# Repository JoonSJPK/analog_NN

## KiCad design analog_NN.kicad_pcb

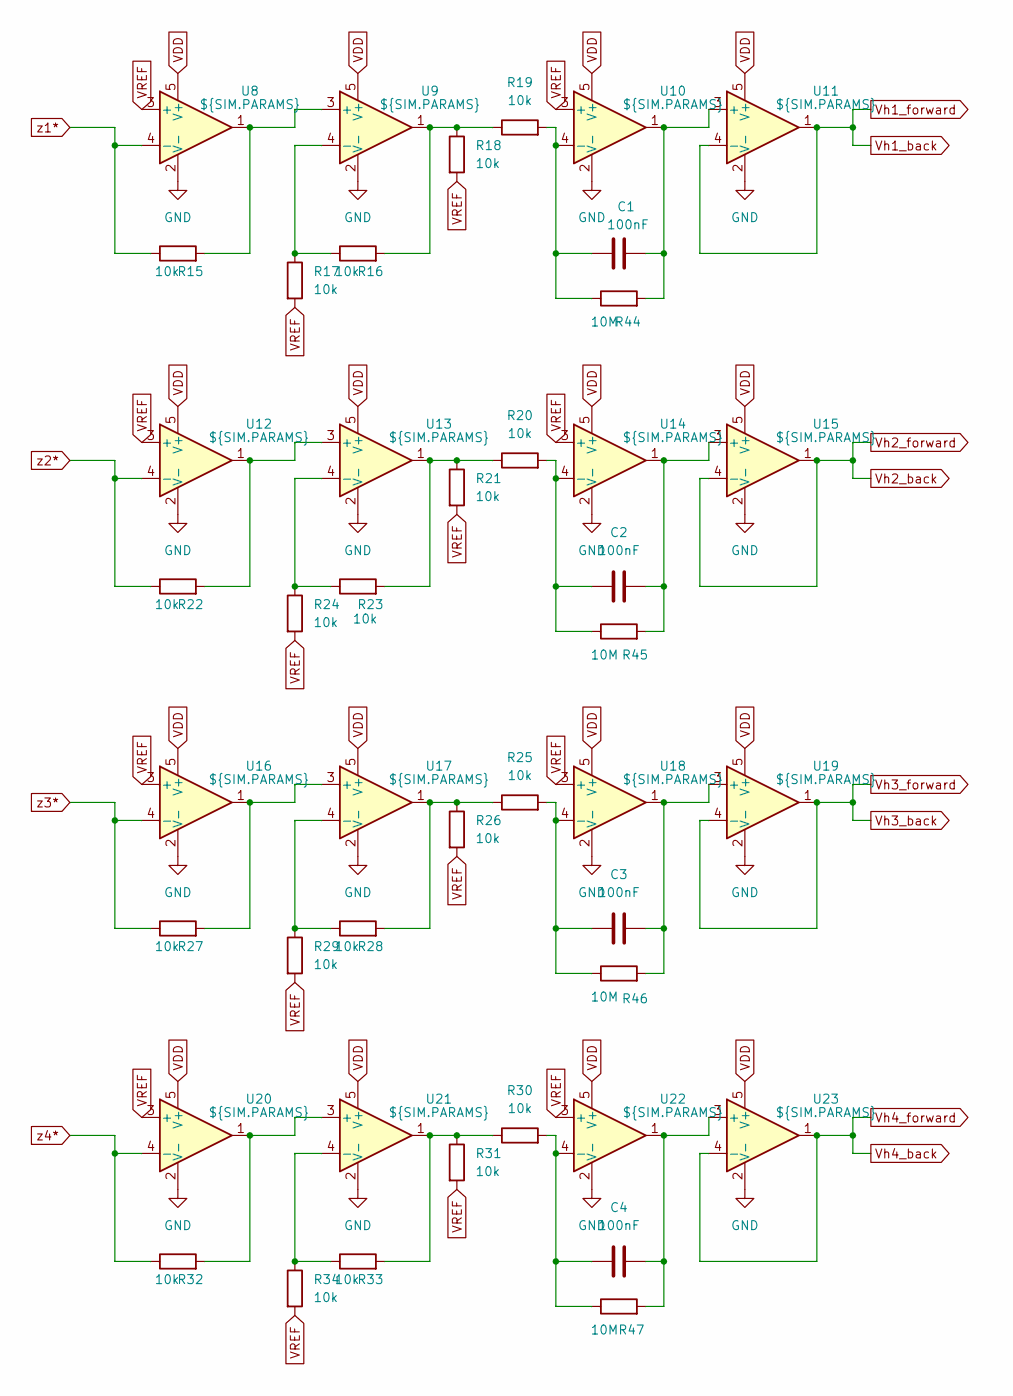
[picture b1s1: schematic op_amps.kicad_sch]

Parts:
C1, C2, C3, C4: 100nF; C_1206_3216Metric
R15, R16, R17, R18, R19, R20, R21, R22, R23, R24, R25, R26, R27, R28, R29, R30, R31, R32, R33, R34: 10k; R_1206_3216Metric
R44, R45, R46, R47: 10M; R_1206_3216Metric
U8, U9, U10, U11, U12, U13, U14, U15, U16, U17, U18, U19, U20, U21, U22, U23: ${SIM.PARAMS}; SOT-23-5

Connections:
GND: U8.2 (V-), U9.2 (V-), U10.2 (V-), U11.2 (V-), U12.2 (V-), U13.2 (V-), U14.2 (V-), U15.2 (V-), U16.2 (V-), U17.2 (V-), U18.2 (V-), U19.2 (V-), U20.2 (V-), U21.2 (V-), U22.2 (V-), U23.2 (V-); also elsewhere on the board
unnamed: R16.2, R18.1, R19.1, U9.1
unnamed: R20.1, R21.1, R23.2, U13.1
unnamed: R25.1, R26.1, R28.2, U17.1
unnamed: R30.1, R31.1, R33.2, U21.1
unnamed: R15.2, U8.1, U9.3 (+)
unnamed: R16.1, R17.1, U9.4 (-)
unnamed: C1.1, R19.2, R44.1, U10.4 (-)
unnamed: C1.2, R44.2, U10.1, U11.3 (+)
unnamed: R22.2, U12.1, U13.3 (+)
unnamed: R23.1, R24.1, U13.4 (-)
unnamed: C2.1, R20.2, R45.1, U14.4 (-)
unnamed: C2.2, R45.2, U14.1, U15.3 (+)
unnamed: R27.2, U16.1, U17.3 (+)
unnamed: R28.1, R29.1, U17.4 (-)
unnamed: C3.1, R25.2, R46.1, U18.4 (-)
unnamed: C3.2, R46.2, U18.1, U19.3 (+)
unnamed: R32.2, U20.1, U21.3 (+)
unnamed: R33.1, R34.1, U21.4 (-)
unnamed: C4.1, R30.2, R47.1, U22.4 (-)
unnamed: C4.2, R47.2, U22.1, U23.3 (+)
VDD: U8.5 (V+), U9.5 (V+), U10.5 (V+), U11.5 (V+), U12.5 (V+), U13.5 (V+), U14.5 (V+), U15.5 (V+), U16.5 (V+), U17.5 (V+), U18.5 (V+), U19.5 (V+), U20.5 (V+), U21.5 (V+), U22.5 (V+), U23.5 (V+); also elsewhere on the board
VREF: R17.2, R18.2, R21.2, R24.2, R26.2, R29.2, R31.2, R34.2, U8.3 (+), U10.3 (+), U12.3 (+), U14.3 (+), U16.3 (+), U18.3 (+), U20.3 (+), U22.3 (+); also elsewhere on the board
Vh1: U11.1, U11.4 (-); also elsewhere on the board
Vh2: U15.1, U15.4 (-); also elsewhere on the board
Vh3: U19.1, U19.4 (-); also elsewhere on the board
Vh4: U23.1, U23.4 (-); also elsewhere on the board
cbar1: R15.1, U8.4 (-); also elsewhere on the board
cbar2: R22.1, U12.4 (-); also elsewhere on the board
cbar3: R27.1, U16.4 (-); also elsewhere on the board
cbar4: R32.1, U20.4 (-); also elsewhere on the board

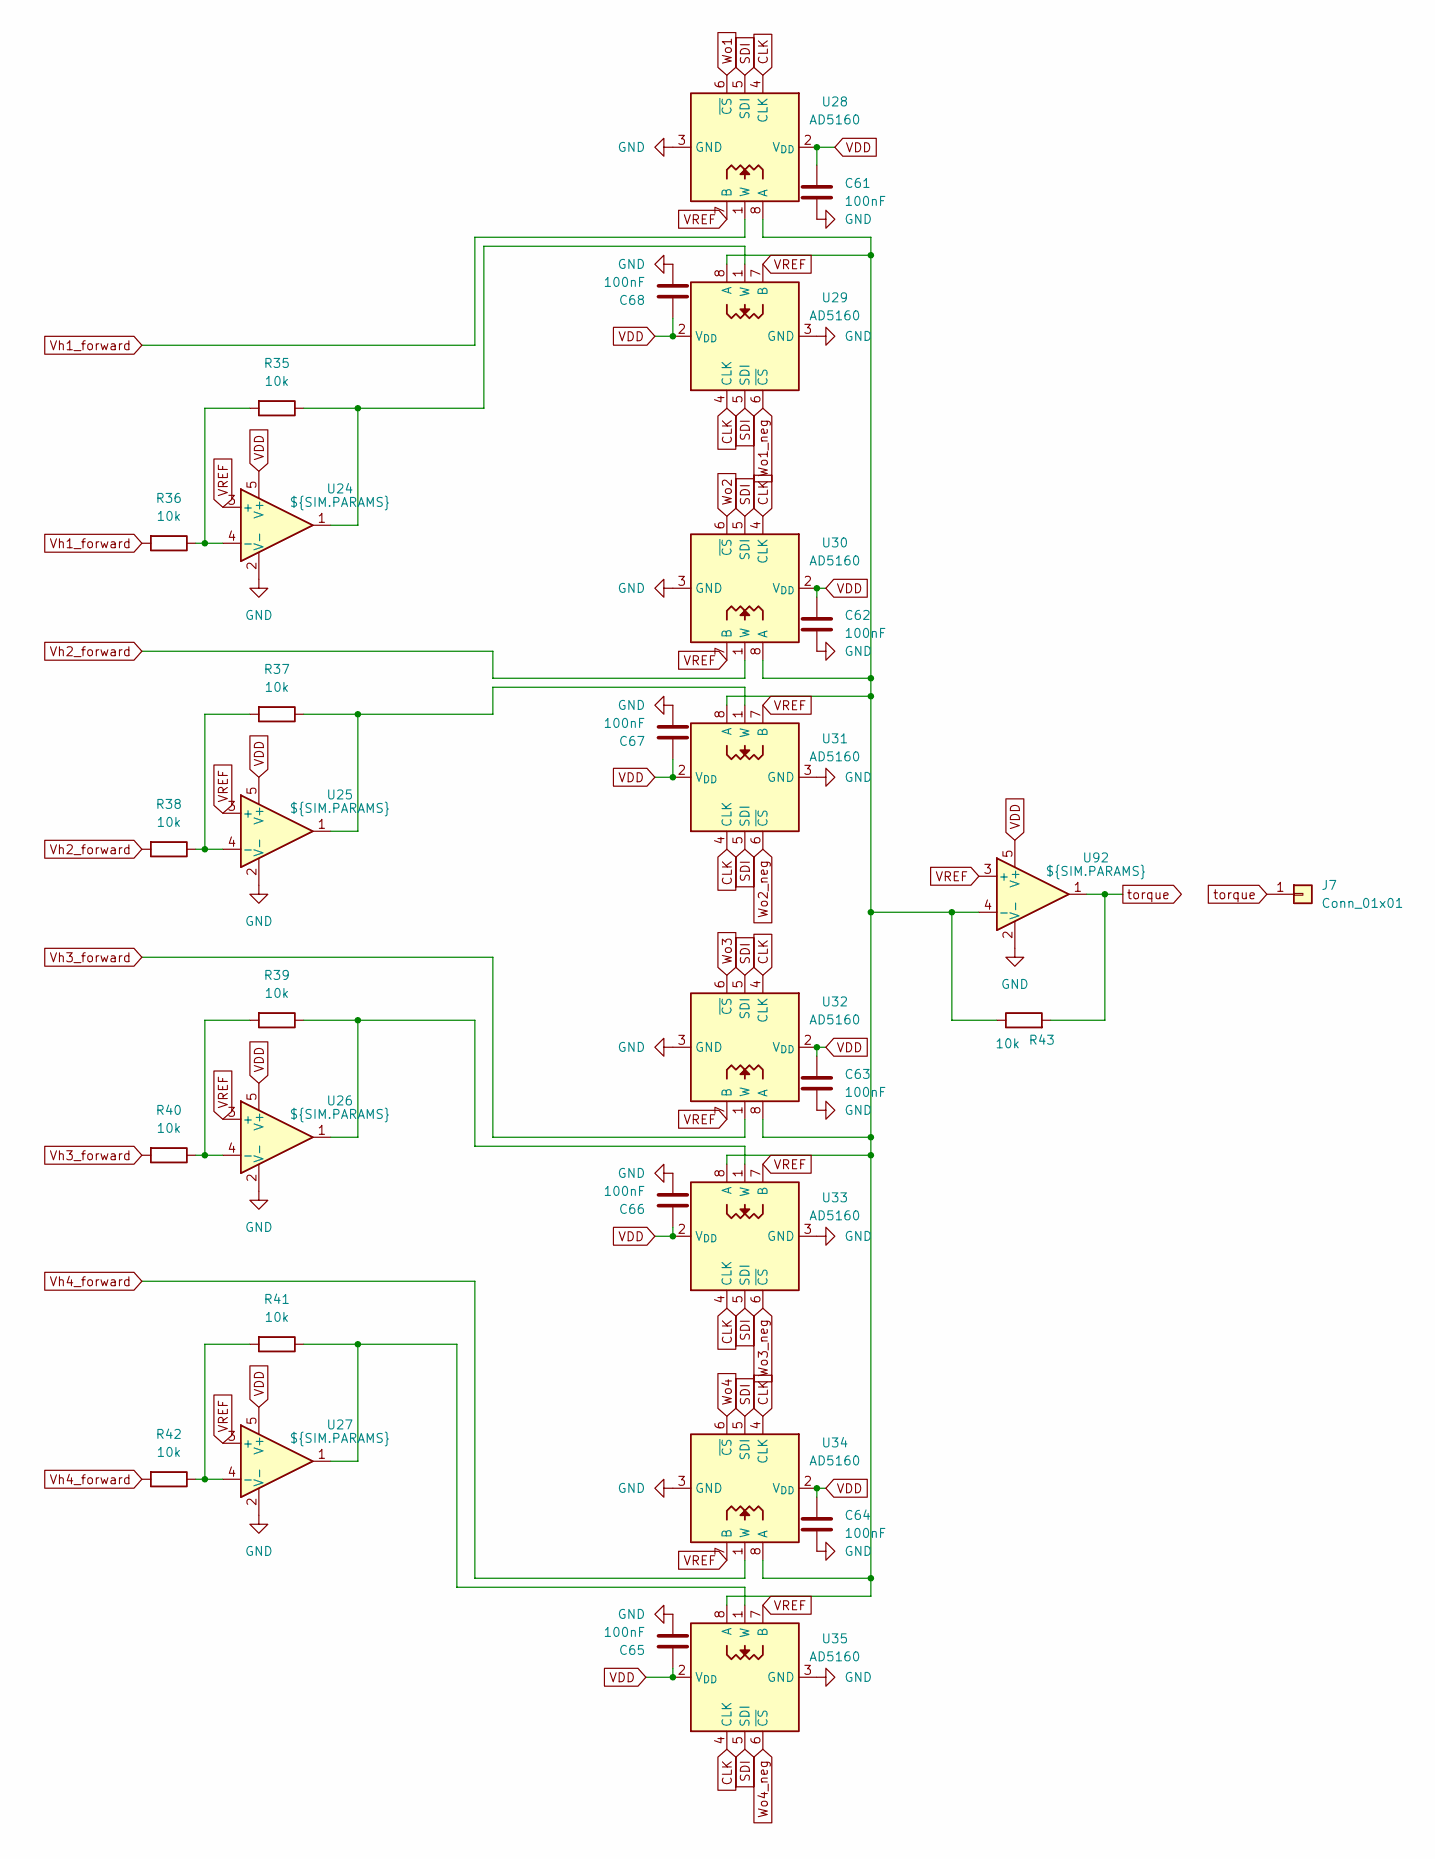
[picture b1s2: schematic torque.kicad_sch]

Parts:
C61, C62, C63, C64, C65, C66, C67, C68: 100nF; C_1206_3216Metric
J7: Conn_01x01; WireSolderPad_1.0mm
R35, R36, R37, R38, R39, R40, R41, R42, R43: 10k; R_1206_3216Metric
U24, U25, U26, U27, U92: ${SIM.PARAMS}; SOT-23-5
U28, U29, U30, U31, U32, U33, U34, U35: AD5160; SOT-23-8

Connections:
CLK: U28.4 (CLK), U29.4 (CLK), U30.4 (CLK), U31.4 (CLK), U32.4 (CLK), U33.4 (CLK), U34.4 (CLK), U35.4 (CLK); also elsewhere on the board
GND: C61.2, C62.2, C63.2, C64.2, C65.2, C66.2, C67.2, C68.2, U24.2 (V-), U25.2 (V-), U26.2 (V-), U27.2 (V-), U28.3 (GND), U29.3 (GND), U30.3 (GND), U31.3 (GND), U32.3 (GND), U33.3 (GND), U34.3 (GND), U35.3 (GND), U92.2 (V-); also elsewhere on the board
unnamed: R35.2, R36.1, U24.4 (-)
unnamed: R37.2, R38.1, U25.4 (-)
unnamed: R39.2, R40.1, U26.4 (-)
unnamed: R41.2, R42.1, U27.4 (-)
unnamed: R43.1, U28.8 (A), U29.8 (A), U30.8 (A), U31.8 (A), U32.8 (A), U33.8 (A), U34.8 (A), U35.8 (A), U92.4 (-)
unnamed: R35.1, U24.1, U29.1 (W)
unnamed: R37.1, U25.1, U31.1 (W)
unnamed: R39.1, U26.1, U33.1 (W)
unnamed: R41.1, U27.1, U35.1 (W)
SDI: U28.5 (SDI), U29.5 (SDI), U30.5 (SDI), U31.5 (SDI), U32.5 (SDI), U33.5 (SDI), U34.5 (SDI), U35.5 (SDI); also elsewhere on the board
VDD: C61.1, C62.1, C63.1, C64.1, C65.1, C66.1, C67.1, C68.1, U24.5 (V+), U25.5 (V+), U26.5 (V+), U27.5 (V+), U28.2 (V_{DD}), U29.2 (V_{DD}), U30.2 (V_{DD}), U31.2 (V_{DD}), U32.2 (V_{DD}), U33.2 (V_{DD}), U34.2 (V_{DD}), U35.2 (V_{DD}), U92.5 (V+); also elsewhere on the board
VREF: U24.3 (+), U25.3 (+), U26.3 (+), U27.3 (+), U28.7 (B), U29.7 (B), U30.7 (B), U31.7 (B), U32.7 (B), U33.7 (B), U34.7 (B), U35.7 (B), U92.3 (+); also elsewhere on the board
Vh1_forward: R36.2, U28.1 (W)
Vh2_forward: R38.2, U30.1 (W)
Vh3_forward: R40.2, U32.1 (W)
Vh4_forward: R42.2, U34.1 (W)
Wo1: U28.6 (~CS); also elsewhere on the board
Wo1_neg: U29.6 (~CS); also elsewhere on the board
Wo2: U30.6 (~CS); also elsewhere on the board
Wo2_neg: U31.6 (~CS); also elsewhere on the board
Wo3: U32.6 (~CS); also elsewhere on the board
Wo3_neg: U33.6 (~CS); also elsewhere on the board
Wo4: U34.6 (~CS); also elsewhere on the board
Wo4_neg: U35.6 (~CS); also elsewhere on the board
torque: J7.1, R43.2, U92.1

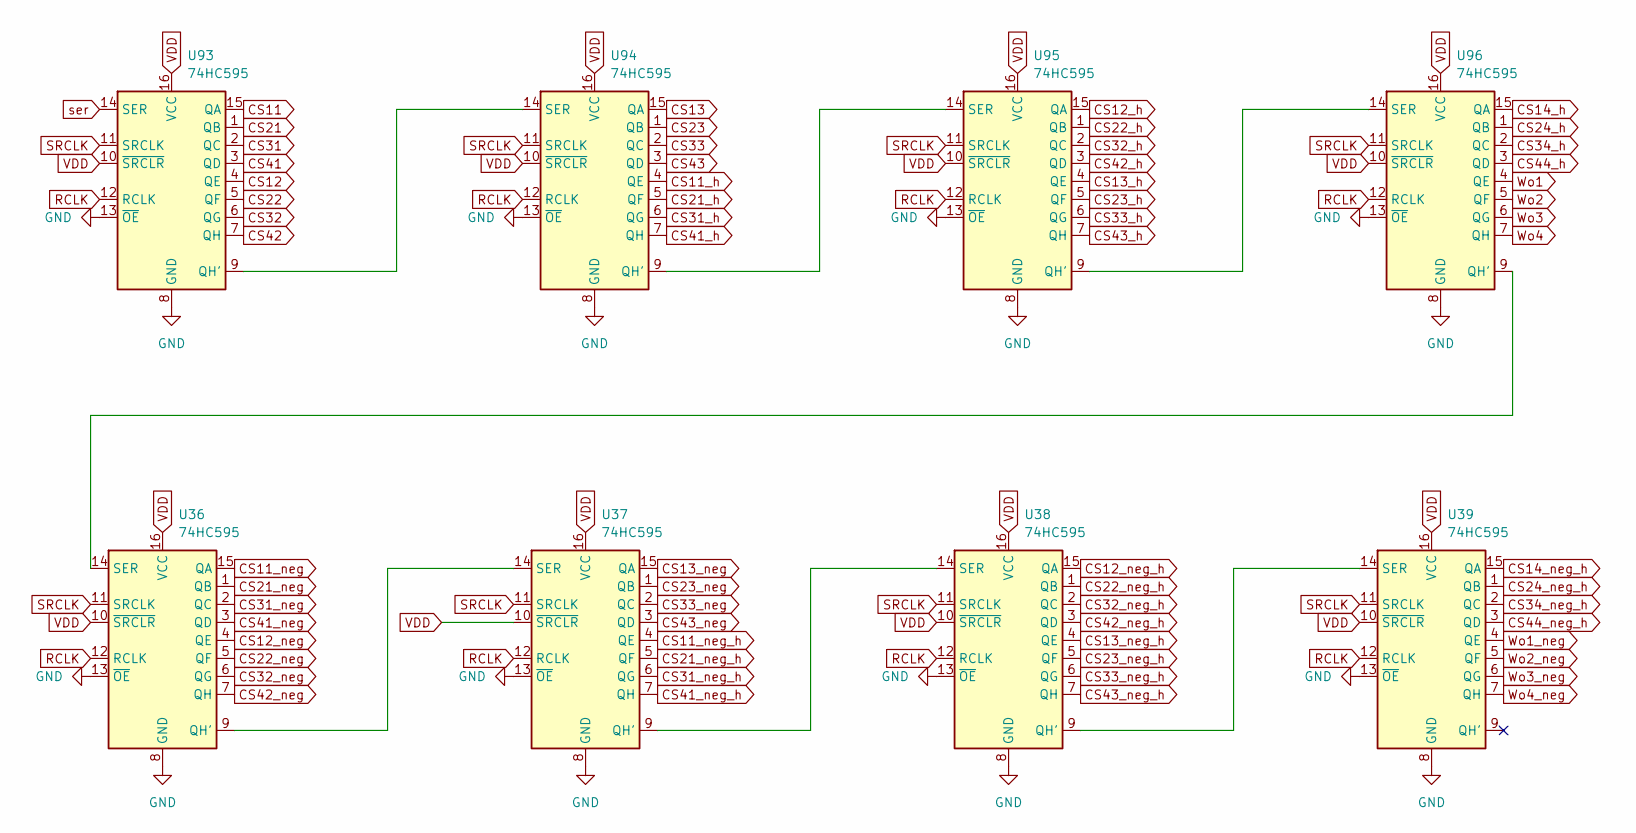
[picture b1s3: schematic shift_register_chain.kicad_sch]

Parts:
U36, U37, U38, U39, U93, U94, U95, U96: 74HC595; SOIC-16_3.9x9.9mm_P1.27mm

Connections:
CS11: U93.15 (QA); also elsewhere on the board
CS11_h: U94.4 (QE); also elsewhere on the board
CS11_neg: U36.15 (QA); also elsewhere on the board
CS11_neg_h: U37.4 (QE); also elsewhere on the board
CS12: U93.4 (QE); also elsewhere on the board
CS12_h: U95.15 (QA); also elsewhere on the board
CS12_neg: U36.4 (QE); also elsewhere on the board
CS12_neg_h: U38.15 (QA); also elsewhere on the board
CS13: U94.15 (QA); also elsewhere on the board
CS13_h: U95.4 (QE); also elsewhere on the board
CS13_neg: U37.15 (QA); also elsewhere on the board
CS13_neg_h: U38.4 (QE); also elsewhere on the board
CS14_h: U96.15 (QA); also elsewhere on the board
CS14_neg_h: U39.15 (QA); also elsewhere on the board
CS21: U93.1 (QB); also elsewhere on the board
CS21_h: U94.5 (QF); also elsewhere on the board
CS21_neg: U36.1 (QB); also elsewhere on the board
CS21_neg_h: U37.5 (QF); also elsewhere on the board
CS22: U93.5 (QF); also elsewhere on the board
CS22_h: U95.1 (QB); also elsewhere on the board
CS22_neg: U36.5 (QF); also elsewhere on the board
CS22_neg_h: U38.1 (QB); also elsewhere on the board
CS23: U94.1 (QB); also elsewhere on the board
CS23_h: U95.5 (QF); also elsewhere on the board
CS23_neg: U37.1 (QB); also elsewhere on the board
CS23_neg_h: U38.5 (QF); also elsewhere on the board
CS24_h: U96.1 (QB); also elsewhere on the board
CS24_neg_h: U39.1 (QB); also elsewhere on the board
CS31: U93.2 (QC); also elsewhere on the board
CS31_h: U94.6 (QG); also elsewhere on the board
CS31_neg: U36.2 (QC); also elsewhere on the board
CS31_neg_h: U37.6 (QG); also elsewhere on the board
CS32: U93.6 (QG); also elsewhere on the board
CS32_h: U95.2 (QC); also elsewhere on the board
CS32_neg: U36.6 (QG); also elsewhere on the board
CS32_neg_h: U38.2 (QC); also elsewhere on the board
CS33: U94.2 (QC); also elsewhere on the board
CS33_h: U95.6 (QG); also elsewhere on the board
CS33_neg: U37.2 (QC); also elsewhere on the board
CS33_neg_h: U38.6 (QG); also elsewhere on the board
CS34_h: U96.2 (QC); also elsewhere on the board
CS34_neg_h: U39.2 (QC); also elsewhere on the board
CS41: U93.3 (QD); also elsewhere on the board
CS41_h: U94.7 (QH); also elsewhere on the board
CS41_neg: U36.3 (QD); also elsewhere on the board
CS41_neg_h: U37.7 (QH); also elsewhere on the board
CS42: U93.7 (QH); also elsewhere on the board
CS42_h: U95.3 (QD); also elsewhere on the board
CS42_neg: U36.7 (QH); also elsewhere on the board
CS42_neg_h: U38.3 (QD); also elsewhere on the board
CS43: U94.3 (QD); also elsewhere on the board
CS43_h: U95.7 (QH); also elsewhere on the board
CS43_neg: U37.3 (QD); also elsewhere on the board
CS43_neg_h: U38.7 (QH); also elsewhere on the board
CS44_h: U96.3 (QD); also elsewhere on the board
CS44_neg_h: U39.3 (QD); also elsewhere on the board
GND: U36.8 (GND), U36.13 (~OE), U37.8 (GND), U37.13 (~OE), U38.8 (GND), U38.13 (~OE), U39.8 (GND), U39.13 (~OE), U93.8 (GND), U93.13 (~OE), U94.8 (GND), U94.13 (~OE), U95.8 (GND), U95.13 (~OE), U96.8 (GND), U96.13 (~OE); also elsewhere on the board
unnamed: U36.9 (QH'), U37.14 (SER)
unnamed: U36.14 (SER), U96.9 (QH')
unnamed: U37.9 (QH'), U38.14 (SER)
unnamed: U38.9 (QH'), U39.14 (SER)
unnamed: U93.9 (QH'), U94.14 (SER)
unnamed: U94.9 (QH'), U95.14 (SER)
unnamed: U95.9 (QH'), U96.14 (SER)
RCLK: U36.12 (RCLK), U37.12 (RCLK), U38.12 (RCLK), U39.12 (RCLK), U93.12 (RCLK), U94.12 (RCLK), U95.12 (RCLK), U96.12 (RCLK); also elsewhere on the board
SRCLK: U36.11 (SRCLK), U37.11 (SRCLK), U38.11 (SRCLK), U39.11 (SRCLK), U93.11 (SRCLK), U94.11 (SRCLK), U95.11 (SRCLK), U96.11 (SRCLK); also elsewhere on the board
VDD: U36.10 (~SRCLR), U36.16 (VCC), U37.10 (~SRCLR), U37.16 (VCC), U38.10 (~SRCLR), U38.16 (VCC), U39.10 (~SRCLR), U39.16 (VCC), U93.10 (~SRCLR), U93.16 (VCC), U94.10 (~SRCLR), U94.16 (VCC), U95.10 (~SRCLR), U95.16 (VCC), U96.10 (~SRCLR), U96.16 (VCC); also elsewhere on the board
Wo1: U96.4 (QE); also elsewhere on the board
Wo1_neg: U39.4 (QE); also elsewhere on the board
Wo2: U96.5 (QF); also elsewhere on the board
Wo2_neg: U39.5 (QF); also elsewhere on the board
Wo3: U96.6 (QG); also elsewhere on the board
Wo3_neg: U39.6 (QG); also elsewhere on the board
Wo4: U96.7 (QH); also elsewhere on the board
Wo4_neg: U39.7 (QH); also elsewhere on the board
ser: U93.14 (SER); also elsewhere on the board

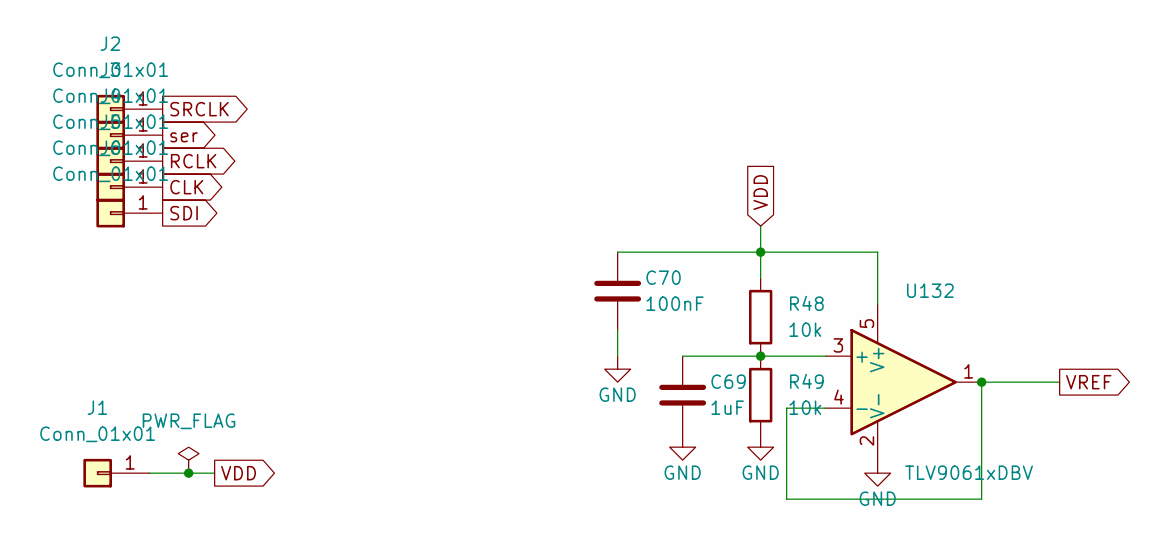
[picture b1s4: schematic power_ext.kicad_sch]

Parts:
C69: 1uF; C_1206_3216Metric_Pad1.33x1.80mm_HandSolder
C70: 100nF; C_1206_3216Metric_Pad1.33x1.80mm_HandSolder
J1, J2, J3, J4, J5, J6: Conn_01x01; WireSolderPad_1.0mm
R48, R49: 10k; R_1206_3216Metric_Pad1.30x1.75mm_HandSolder
U132: TLV9061xDBV; SOT-23-5

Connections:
GND: C69.2, C70.2, R49.2, U132.2 (V-); also elsewhere on the board
unnamed: C69.1, R48.2, R49.1, U132.3 (+)
RCLK: J4.1; also elsewhere on the board
SRCLK: J2.1; also elsewhere on the board
VDD: C70.1, J1.1, R48.1, U132.5 (V+); also elsewhere on the board
VREF: U132.1, U132.4 (-); also elsewhere on the board
ser: J3.1; also elsewhere on the board

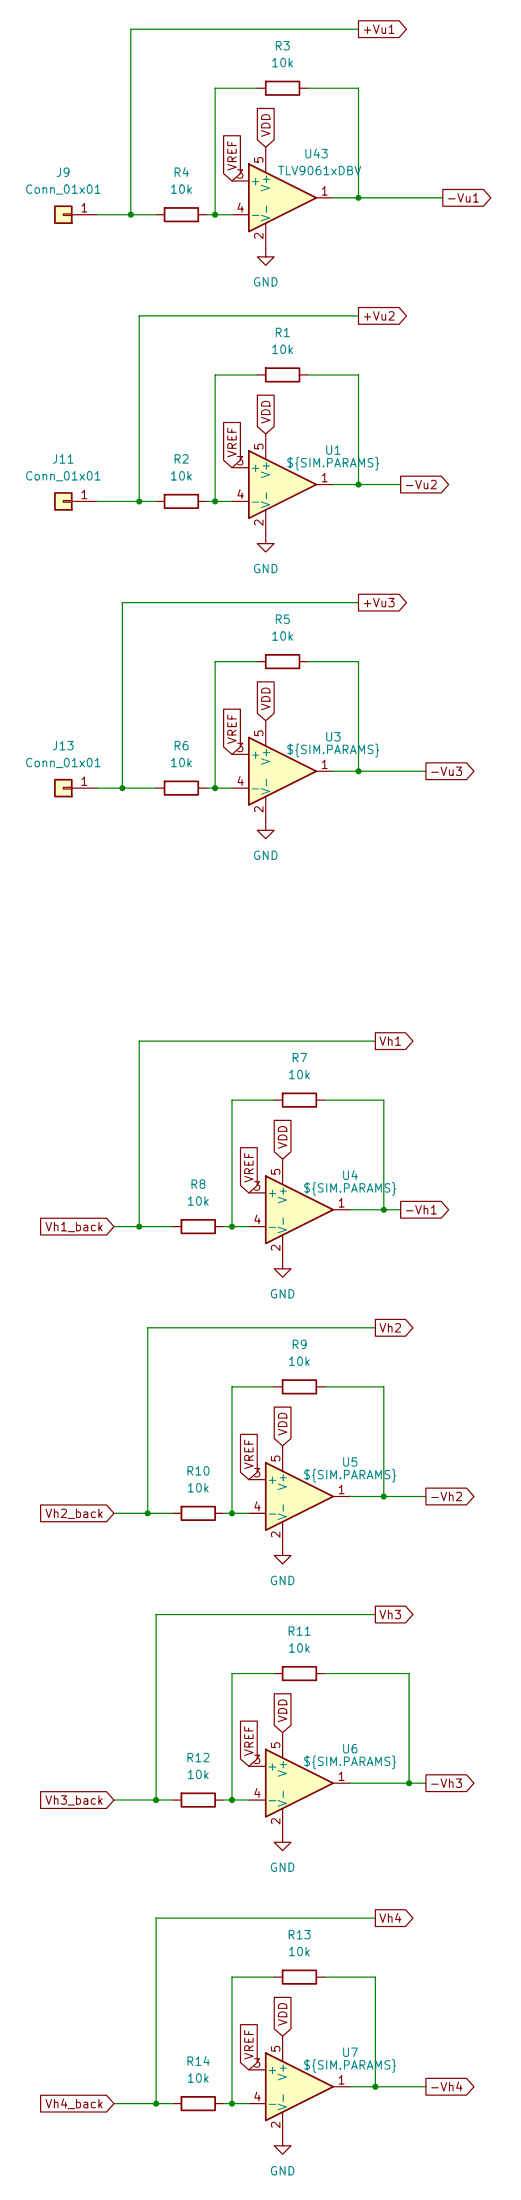
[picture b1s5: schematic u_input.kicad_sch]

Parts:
J9, J11, J13: Conn_01x01; WireSolderPad_1.0mm
R1, R2, R3, R4, R5, R6, R7, R8, R9, R10, R11, R12, R13, R14: 10k; R_1206_3216Metric
U1, U3, U4, U5, U6, U7: ${SIM.PARAMS}; SOT-23-5
U43: TLV9061xDBV; SOT-23-5

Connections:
-Vh1: R7.1, U4.1; also elsewhere on the board
-Vh2: R9.1, U5.1; also elsewhere on the board
-Vh3: R11.1, U6.1; also elsewhere on the board
-Vh4: R13.1, U7.1; also elsewhere on the board
-Vu1: R3.1, U43.1; also elsewhere on the board
-Vu2: R1.1, U1.1; also elsewhere on the board
-Vu3: R5.1, U3.1; also elsewhere on the board
GND: U1.2 (V-), U3.2 (V-), U4.2 (V-), U5.2 (V-), U6.2 (V-), U7.2 (V-), U43.2 (V-); also elsewhere on the board
unnamed: R1.2, R2.1, U1.4 (-)
unnamed: R5.2, R6.1, U3.4 (-)
unnamed: R7.2, R8.1, U4.4 (-)
unnamed: R9.2, R10.1, U5.4 (-)
unnamed: R11.2, R12.1, U6.4 (-)
unnamed: R13.2, R14.1, U7.4 (-)
unnamed: R3.2, R4.1, U43.4 (-)
VDD: U1.5 (V+), U3.5 (V+), U4.5 (V+), U5.5 (V+), U6.5 (V+), U7.5 (V+), U43.5 (V+); also elsewhere on the board
VREF: U1.3 (+), U3.3 (+), U4.3 (+), U5.3 (+), U6.3 (+), U7.3 (+), U43.3 (+); also elsewhere on the board
Vh1: R8.2; also elsewhere on the board
Vh2: R10.2; also elsewhere on the board
Vh3: R12.2; also elsewhere on the board
Vh4: R14.2; also elsewhere on the board
Vu1: J9.1, R4.2; also elsewhere on the board
Vu2: J11.1, R2.2; also elsewhere on the board
Vu3: J13.1, R6.2; also elsewhere on the board

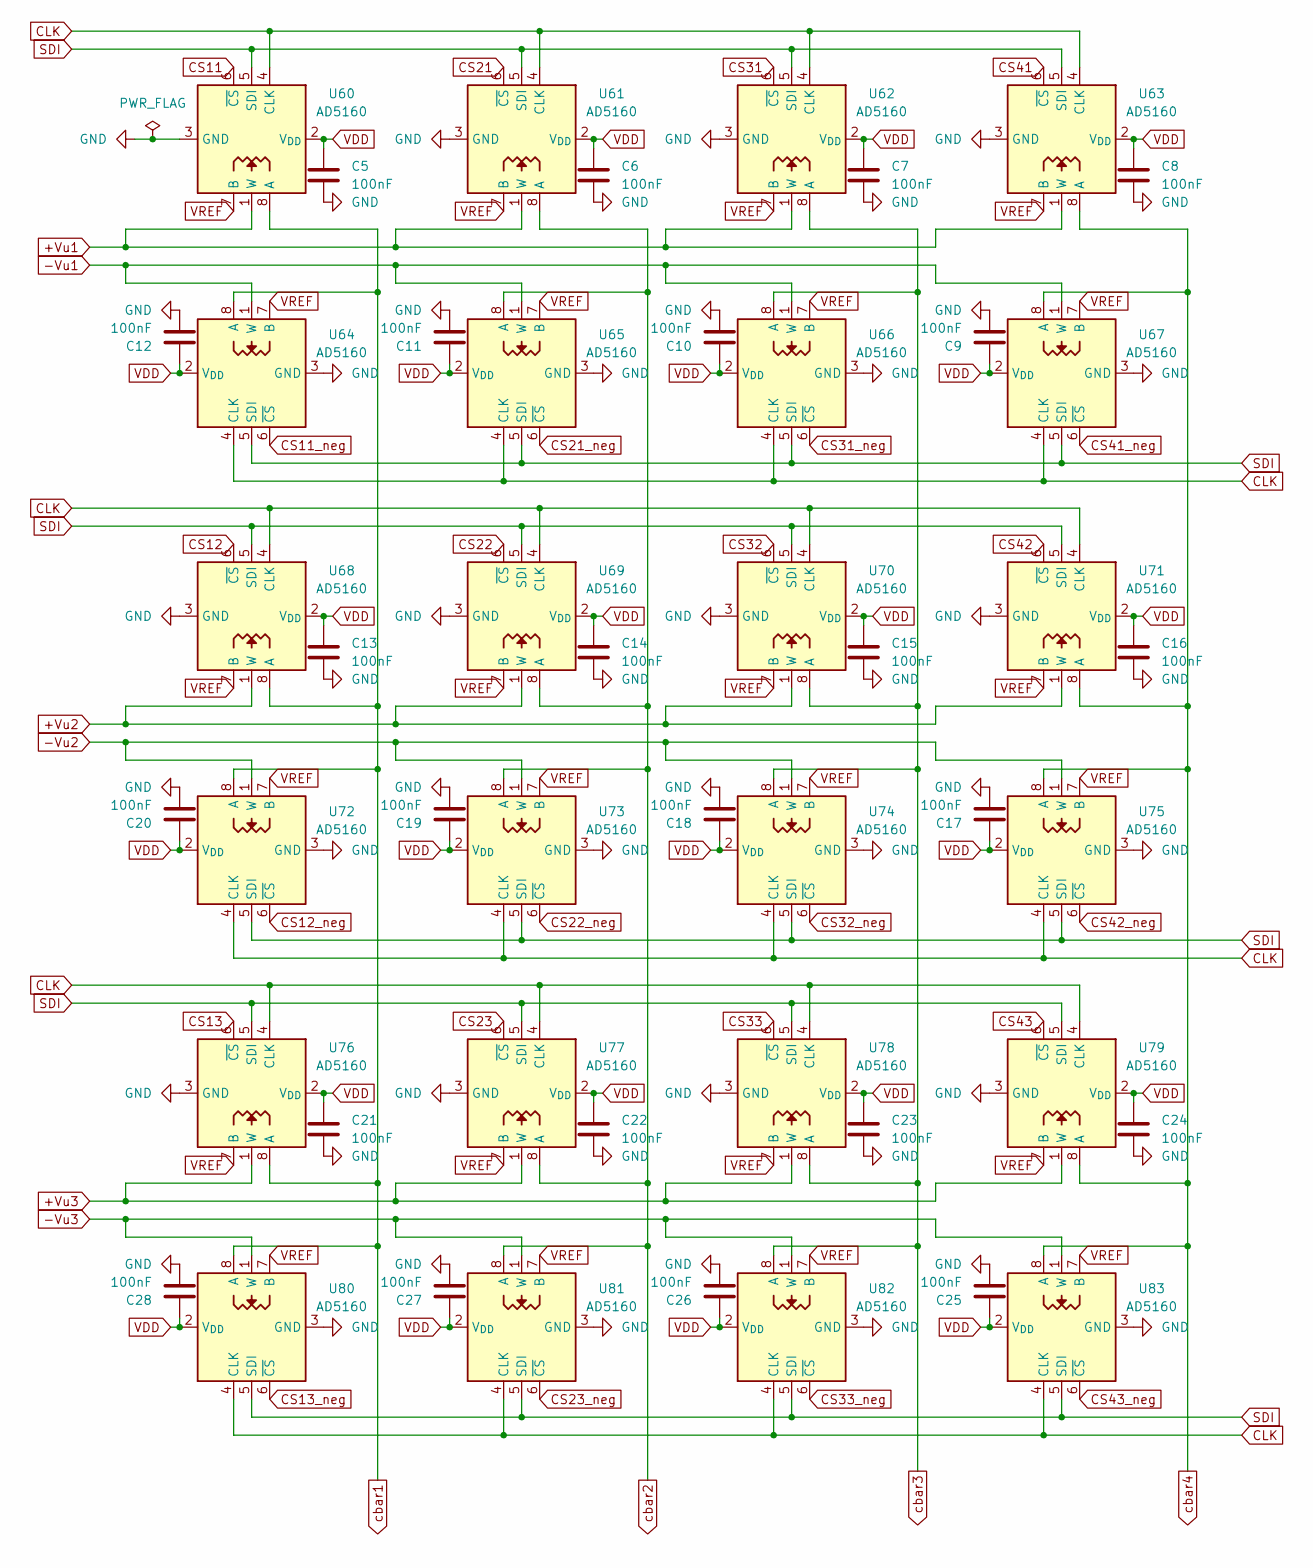
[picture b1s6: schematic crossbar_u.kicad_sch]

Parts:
C5, C6, C7, C8, C9, C10, C11, C12, C13, C14, C15, C16, C17, C18, C19, C20, C21, C22, C23, C24, C25, C26, C27, C28: 100nF; C_1206_3216Metric
U60, U61, U62, U63, U64, U65, U66, U67, U68, U69, U70, U71, U72, U73, U74, U75, U76, U77, U78, U79, U80, U81, U82, U83: AD5160; SOT-23-8

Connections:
+Vu1: U60.1 (W), U61.1 (W), U62.1 (W), U63.1 (W)
+Vu2: U68.1 (W), U69.1 (W), U70.1 (W), U71.1 (W)
+Vu3: U76.1 (W), U77.1 (W), U78.1 (W), U79.1 (W)
-Vu1: U64.1 (W), U65.1 (W), U66.1 (W), U67.1 (W); also elsewhere on the board
-Vu2: U72.1 (W), U73.1 (W), U74.1 (W), U75.1 (W); also elsewhere on the board
-Vu3: U80.1 (W), U81.1 (W), U82.1 (W), U83.1 (W); also elsewhere on the board
CLK: U60.4 (CLK), U61.4 (CLK), U62.4 (CLK), U63.4 (CLK), U64.4 (CLK), U65.4 (CLK), U66.4 (CLK), U67.4 (CLK), U68.4 (CLK), U69.4 (CLK), U70.4 (CLK), U71.4 (CLK), U72.4 (CLK), U73.4 (CLK), U74.4 (CLK), U75.4 (CLK), U76.4 (CLK), U77.4 (CLK), U78.4 (CLK), U79.4 (CLK), U80.4 (CLK), U81.4 (CLK), U82.4 (CLK), U83.4 (CLK); also elsewhere on the board
CS11: U60.6 (~CS); also elsewhere on the board
CS11_neg: U64.6 (~CS); also elsewhere on the board
CS12: U68.6 (~CS); also elsewhere on the board
CS12_neg: U72.6 (~CS); also elsewhere on the board
CS13: U76.6 (~CS); also elsewhere on the board
CS13_neg: U80.6 (~CS); also elsewhere on the board
CS21: U61.6 (~CS); also elsewhere on the board
CS21_neg: U65.6 (~CS); also elsewhere on the board
CS22: U69.6 (~CS); also elsewhere on the board
CS22_neg: U73.6 (~CS); also elsewhere on the board
CS23: U77.6 (~CS); also elsewhere on the board
CS23_neg: U81.6 (~CS); also elsewhere on the board
CS31: U62.6 (~CS); also elsewhere on the board
CS31_neg: U66.6 (~CS); also elsewhere on the board
CS32: U70.6 (~CS); also elsewhere on the board
CS32_neg: U74.6 (~CS); also elsewhere on the board
CS33: U78.6 (~CS); also elsewhere on the board
CS33_neg: U82.6 (~CS); also elsewhere on the board
CS41: U63.6 (~CS); also elsewhere on the board
CS41_neg: U67.6 (~CS); also elsewhere on the board
CS42: U71.6 (~CS); also elsewhere on the board
CS42_neg: U75.6 (~CS); also elsewhere on the board
CS43: U79.6 (~CS); also elsewhere on the board
CS43_neg: U83.6 (~CS); also elsewhere on the board
GND: C5.2, C6.2, C7.2, C8.2, C9.2, C10.2, C11.2, C12.2, C13.2, C14.2, C15.2, C16.2, C17.2, C18.2, C19.2, C20.2, C21.2, C22.2, C23.2, C24.2, C25.2, C26.2, C27.2, C28.2, U60.3 (GND), U61.3 (GND), U62.3 (GND), U63.3 (GND), U64.3 (GND), U65.3 (GND), U66.3 (GND), U67.3 (GND), U68.3 (GND), U69.3 (GND), U70.3 (GND), U71.3 (GND), U72.3 (GND), U73.3 (GND), U74.3 (GND), U75.3 (GND), U76.3 (GND), U77.3 (GND), U78.3 (GND), U79.3 (GND), U80.3 (GND), U81.3 (GND), U82.3 (GND), U83.3 (GND); also elsewhere on the board
SDI: U60.5 (SDI), U61.5 (SDI), U62.5 (SDI), U63.5 (SDI), U64.5 (SDI), U65.5 (SDI), U66.5 (SDI), U67.5 (SDI), U68.5 (SDI), U69.5 (SDI), U70.5 (SDI), U71.5 (SDI), U72.5 (SDI), U73.5 (SDI), U74.5 (SDI), U75.5 (SDI), U76.5 (SDI), U77.5 (SDI), U78.5 (SDI), U79.5 (SDI), U80.5 (SDI), U81.5 (SDI), U82.5 (SDI), U83.5 (SDI); also elsewhere on the board
VDD: C5.1, C6.1, C7.1, C8.1, C9.1, C10.1, C11.1, C12.1, C13.1, C14.1, C15.1, C16.1, C17.1, C18.1, C19.1, C20.1, C21.1, C22.1, C23.1, C24.1, C25.1, C26.1, C27.1, C28.1, U60.2 (V_{DD}), U61.2 (V_{DD}), U62.2 (V_{DD}), U63.2 (V_{DD}), U64.2 (V_{DD}), U65.2 (V_{DD}), U66.2 (V_{DD}), U67.2 (V_{DD}), U68.2 (V_{DD}), U69.2 (V_{DD}), U70.2 (V_{DD}), U71.2 (V_{DD}), U72.2 (V_{DD}), U73.2 (V_{DD}), U74.2 (V_{DD}), U75.2 (V_{DD}), U76.2 (V_{DD}), U77.2 (V_{DD}), U78.2 (V_{DD}), U79.2 (V_{DD}), U80.2 (V_{DD}), U81.2 (V_{DD}), U82.2 (V_{DD}), U83.2 (V_{DD}); also elsewhere on the board
VREF: U60.7 (B), U61.7 (B), U62.7 (B), U63.7 (B), U64.7 (B), U65.7 (B), U66.7 (B), U67.7 (B), U68.7 (B), U69.7 (B), U70.7 (B), U71.7 (B), U72.7 (B), U73.7 (B), U74.7 (B), U75.7 (B), U76.7 (B), U77.7 (B), U78.7 (B), U79.7 (B), U80.7 (B), U81.7 (B), U82.7 (B), U83.7 (B); also elsewhere on the board
cbar1: U60.8 (A), U64.8 (A), U68.8 (A), U72.8 (A), U76.8 (A), U80.8 (A); also elsewhere on the board
cbar2: U61.8 (A), U65.8 (A), U69.8 (A), U73.8 (A), U77.8 (A), U81.8 (A); also elsewhere on the board
cbar3: U62.8 (A), U66.8 (A), U70.8 (A), U74.8 (A), U78.8 (A), U82.8 (A); also elsewhere on the board
cbar4: U63.8 (A), U67.8 (A), U71.8 (A), U75.8 (A), U79.8 (A), U83.8 (A); also elsewhere on the board
